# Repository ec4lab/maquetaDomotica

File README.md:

# Maqueta Domótica

El propósito de este repositorio es documentar el paso a paso de la construcción de una Maqueta domótica didáctica implementada sobre la plataforma Home Assistant.

<p align="center">

<figcaption align="center" style="margin-top: 10px; font-size: 14px; color: #555;">
    Maqueta Domótica
</figcaption>
</p>

Debido a la constante actualización de las plataformas utilizadas, en las guías se priorizarán conceptos y enfoques en lugar de un paso a paso estricto de utilización de cada herramienta, para evitar lo más posible la obsolescencia de la información.

## Estructura de carpetas

El repositorio se estructura en dos carpetas principales `docs` e `info`.

### docs

La primer carpeta contiene la documentación técnica y guías para la construcción e implementación de los dispositivos que componen la maqueta, par que puedan ser replicados y/o modificados en otras aplicaciones.

### info

Esta carpeta contiene información y algunos conceptos generales que complementan la documentación. No son aplicables directamente a la maqueta pero sirven como orientación para una mejor compresión de las aplicaciones y también brindan contexto a los dispositivos.

### Estructura actual del repositorio

```text
/maquetaDomótica
├── docs/
│   ├── maqueta/
│   ├── router-servidor/
│   ├── sv-template-multisensor/
│   ├── 
│   └── 
├── info/
│   ├── neopixels/
│   └── 
└── dev/
    └── Carpetas de alumnos durante el desarrollo
```

## Línea de Tiempo

Pasos a seguir para la construcción de la maqueta según la fecha de implementación

### 2026/08 - [docs/maqueta](docs/maqueta/)

* Construcción de la maqueta física
* Definición de las plantas y áreas  

### 2026/08 [docs/router-servidor](docs/router-servidor/)

* Construcción del soporte físico
* Configuración de la LAN en el Router
* Instalación de Home Assistant OS en una raspberryPI 4.
* Configuraciones básicas (IP estática, unidades, usuarios, mapa, App Companion)
* Asignación de áreas, plantas y habitaciones
* Primeras Aplicaciones (File Editor, ESPHome Device Builder, Tailscale)
* Mapa de la red y consideraciones para futuros dispositivos e integraciones.

### 2026/08 [docs/specs](docs/specs)

* Política de nombres de los dispositivos

### 2026/09 [docs/sv-template-multisensor](docs/sv-template-multisensor/)

* Primer dispositivo integrado a la maqueta.
* Entidades:
  * DHT11: Humedad y temperatura
  * Pulsador
  * Leds
  * Sensor de señal analógica
  * Botón de reset
* Sirve como plantilla para próximos dispositivos.

### 2026/09 [info/neopixels](info/neopixels)

* Introducción a las tiras de leds direccionables.
* Opciones de integración con ESPHome y Home Assistant

### 2026/10 [docs/control de luces](link)

### 2026/10 [docs/neopixels sala de estar](link)

## Trabajos Futuros

Protocolos  
Automatizaciones  
Pruebas  
Incidentes  
usuarios  
backups  
actualización  
seguridad  
dashboards  
dashboards adicionales
ZigBee  
Bluetooth/BLE  
ESP-NOW  
LoRa  
Protocolos industriales (ModBus / OPCua)  
KNX  
BACNet  
MQTT  
Matter  

### info dispositivos

* ESPHome
  * En Home Assistant OS
  * En ESPHome web
  * En VSCode
  * En Cursor con IA.
  * Crear un dispositivo genérico
    * Componentes básicos del dispositivo.
    * Entidades básicas del dispositivo.

## Licencia

Este proyecto está licenciado bajo la Licencia MIT.
Está permitido el uso, copia, modificaciones y distribución del software libremente, siempre que se incluya el aviso de derechos de autor original.  

Para más información, consultar el archivo [LICENSE](LICENSE)

## Contacto

**EC4lab**  
GitHub: [ec4lab](https://github.com/ec4lab)  
email: [ec4lab@gmail.com](ec4lab@gmail.com)

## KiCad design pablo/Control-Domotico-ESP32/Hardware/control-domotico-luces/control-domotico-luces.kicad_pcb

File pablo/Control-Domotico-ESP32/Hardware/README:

## 🛠️ 4. Diseño electrónico en KiCad

Para construir el módulo de domótica se diseñó una placa de circuito impreso utilizando **KiCad**, una herramienta de diseño electrónico que permite desarrollar tanto el esquemático como el PCB.

### 4.1. Diseño del esquemático

En primer lugar, se realizó el esquemático del circuito para representar las conexiones eléctricas entre el ESP32, las teclas, las resistencias, los transistores y las luces.

El diseño contempla:

- Las conexiones de las seis entradas digitales para las teclas.
- Las resistencias pull-down de 10 kΩ para establecer el nivel lógico de las entradas.
- Las seis salidas digitales destinadas al control de los transistores 2N2222A.
- Las resistencias de base de los transistores.
- La distribución de alimentación de 5 V y las conexiones de GND.
- Las borneras para facilitar la conexión externa de los distintos elementos del circuito.

El esquemático permite verificar las conexiones antes de trasladarlas a la placa física.

### 4.2. Diseño de la placa PCB

Una vez finalizado el esquemático, se desarrolló el diseño de la placa de circuito impreso (PCB) en KiCad.

En esta etapa se definieron la ubicación de los componentes, las pistas de cobre y las borneras necesarias para conectar el ESP32 con los circuitos externos.

El uso de borneras permite conectar y desconectar las teclas, las luces y la alimentación sin tener que soldar directamente cada cable a la placa. Esto facilita el montaje, las pruebas y el mantenimiento del sistema.

También se debe respetar la separación entre las pistas y dimensionar su ancho de acuerdo con las corrientes que circulan por ellas, especialmente en las líneas de alimentación de las luces.

### 4.3. Fabricación mediante grabado químico

Para fabricar la PCB se utilizará la técnica de **grabado químico con ácido**. Este procedimiento permite obtener las pistas conductoras sobre una placa revestida de cobre, eliminando el cobre de las zonas que no forman parte del circuito.

El proceso de fabricación comprende las siguientes etapas:

1. **Preparación del diseño:** revisar el PCB en KiCad y generar el patrón de las pistas para transferirlo a la placa.
2. **Preparación de la placa:** limpiar la superficie de cobre para facilitar la transferencia del diseño.
3. **Transferencia del patrón:** aplicar el diseño de las pistas sobre la placa utilizando un método de transferencia adecuado.
4. **Grabado químico:** eliminar el cobre expuesto mediante un producto de grabado apropiado, siguiendo las instrucciones de seguridad del fabricante.
5. **Limpieza y revisión:** retirar los residuos del proceso y comprobar que las pistas hayan quedado correctamente definidas, sin cortes ni cortocircuitos.
6. **Perforado y montaje:** realizar los orificios necesarios, soldar los componentes y colocar las borneras.
7. **Verificación eléctrica:** comprobar la continuidad de las pistas y la ausencia de cortocircuitos antes de conectar la alimentación y el ESP32.

Durante el grabado se deben utilizar los elementos de protección adecuados y trabajar en un lugar apropiado. El producto químico utilizado y sus residuos deben manipularse y desecharse según sus indicaciones de seguridad y la normativa local.

---

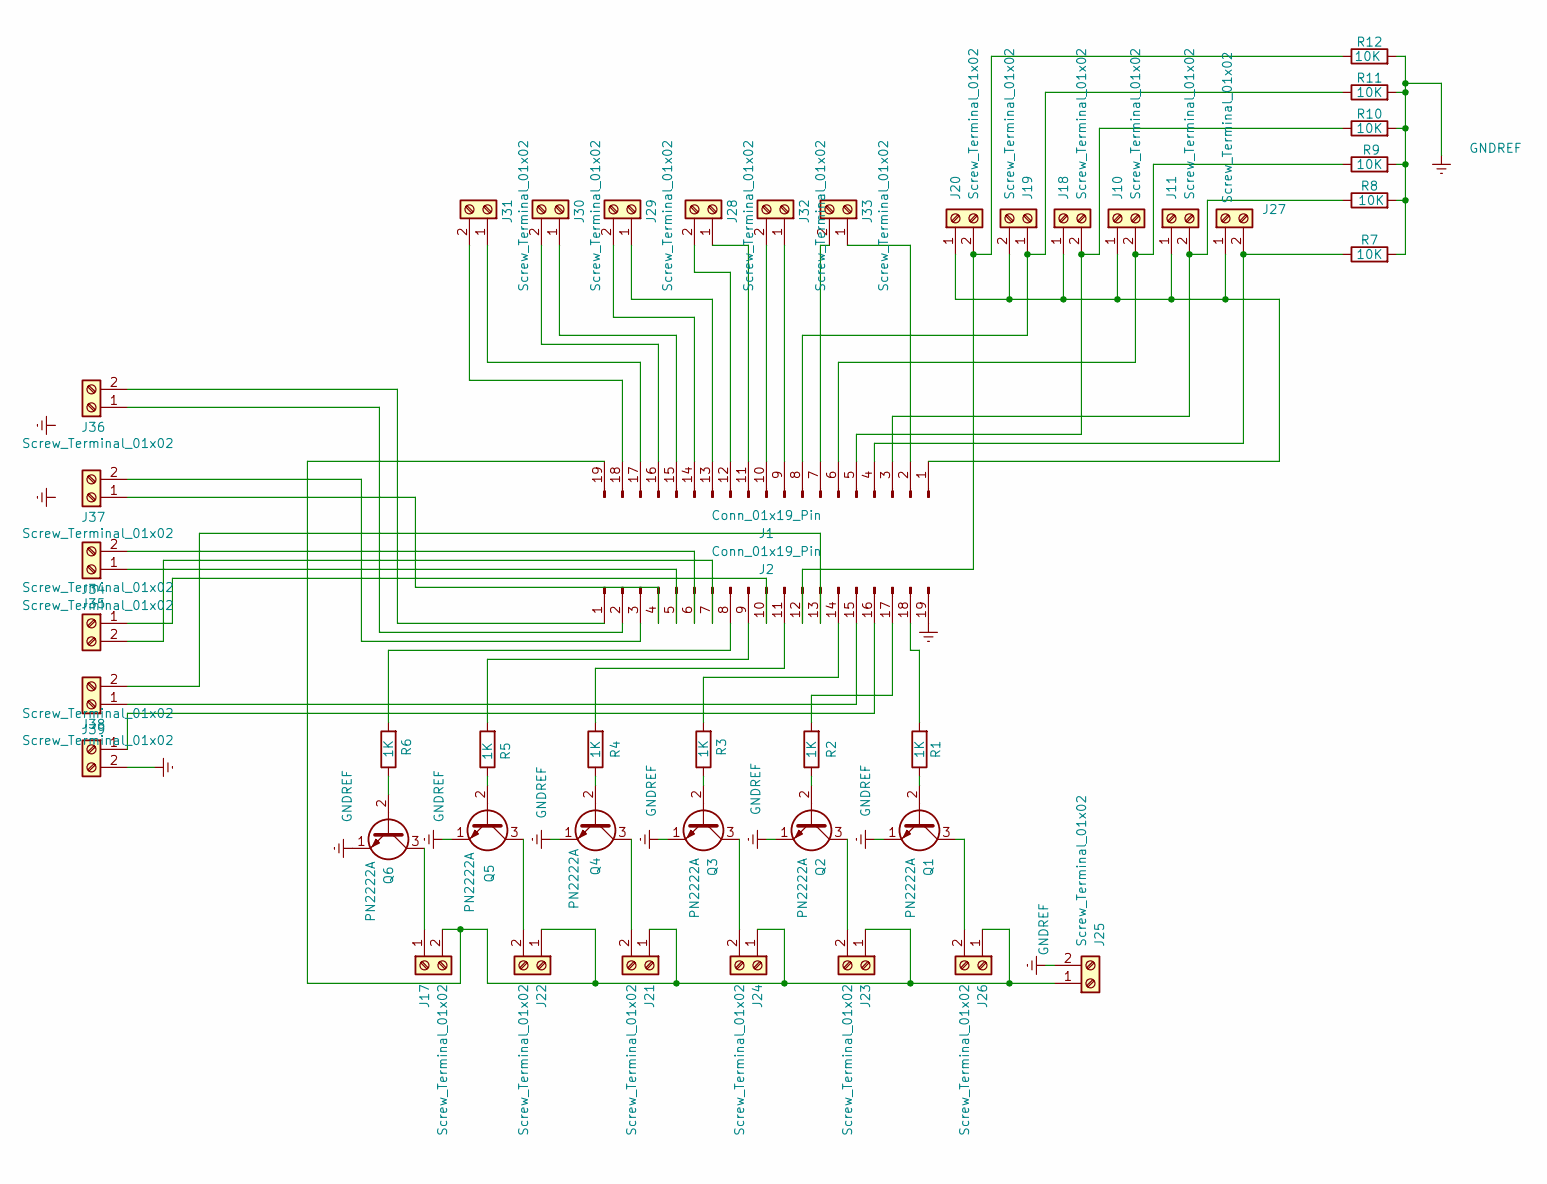
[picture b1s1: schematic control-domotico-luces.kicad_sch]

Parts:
J1, J2: Conn_01x19_Pin; PinHeader_1x19_P2.54mm_Vertical
J10, J11, J17, J18, J19, J20, J21, J22, J23, J24, J25, J26, J27, J28, J29, J30, J31, J32, J33, J34, J35, J36, J37, J38, J39: Screw_Terminal_01x02; TerminalBlock_MaiXu_MX126-5.0-02P_1x02_P5.00mm
Q1, Q2, Q3, Q4, Q5, Q6: PN2222A; TO-92_Wide
R1, R2, R3, R4, R5, R6: 1K; R_Axial_DIN0207_L6.3mm_D2.5mm_P10.16mm_Horizontal
R7, R8, R9, R10, R11, R12: 10K; R_Axial_DIN0207_L6.3mm_D2.5mm_P10.16mm_Horizontal

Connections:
GNDREF: J2.19, J25.2, J39.2, Q1.1 (E), Q2.1 (E), Q3.1 (E), Q4.1 (E), Q5.1 (E), Q6.1 (E), R7.2, R8.2, R9.2, R10.2, R11.2, R12.2
unnamed: J1.1, J10.1, J11.1, J18.1, J19.2, J20.1, J27.1
unnamed: J1.2, J33.1
unnamed: J1.3, J11.2, R8.1
unnamed: J1.4, J27.2, R7.1
unnamed: J1.5, J18.2, R10.1
unnamed: J1.6, J10.2, R9.1
unnamed: J1.7, J33.2
unnamed: J1.8, J19.1, R11.1
unnamed: J1.9, J32.1
unnamed: J1.10, J32.2
unnamed: J1.11, J28.1
unnamed: J1.12, J28.2
unnamed: J1.13, J29.1
unnamed: J1.14, J29.2
unnamed: J1.15, J30.1
unnamed: J1.16, J30.2
unnamed: J1.17, J31.1
unnamed: J1.18, J31.2
unnamed: J1.19, J17.2, J21.1, J22.1, J23.1, J24.1, J25.1, J26.1
unnamed: J2.1, J36.2
unnamed: J2.2, J36.1
unnamed: J2.3, J37.2
unnamed: J2.4, J37.1
unnamed: J2.5, J34.1
unnamed: J2.6, J34.2
unnamed: J2.7, J35.2
unnamed: J2.8, R6.2
unnamed: J2.9, R5.2
unnamed: J2.10, J35.1
unnamed: J2.11, R4.2
unnamed: J2.12, J20.2, R12.1
unnamed: J2.13, J38.2
unnamed: J2.14, R3.2
unnamed: J2.15, J38.1
unnamed: J2.16, J39.1
unnamed: J2.17, R2.2
unnamed: J2.18, R1.2
unnamed: J17.1, Q6.3 (C)
unnamed: J21.2, Q4.3 (C)
unnamed: J22.2, Q5.3 (C)
unnamed: J23.2, Q2.3 (C)
unnamed: J24.2, Q3.3 (C)
unnamed: J26.2, Q1.3 (C)
unnamed: Q1.2 (B), R1.1
unnamed: Q2.2 (B), R2.1
unnamed: Q3.2 (B), R3.1
unnamed: Q4.2 (B), R4.1
unnamed: Q5.2 (B), R5.1
unnamed: Q6.2 (B), R6.1

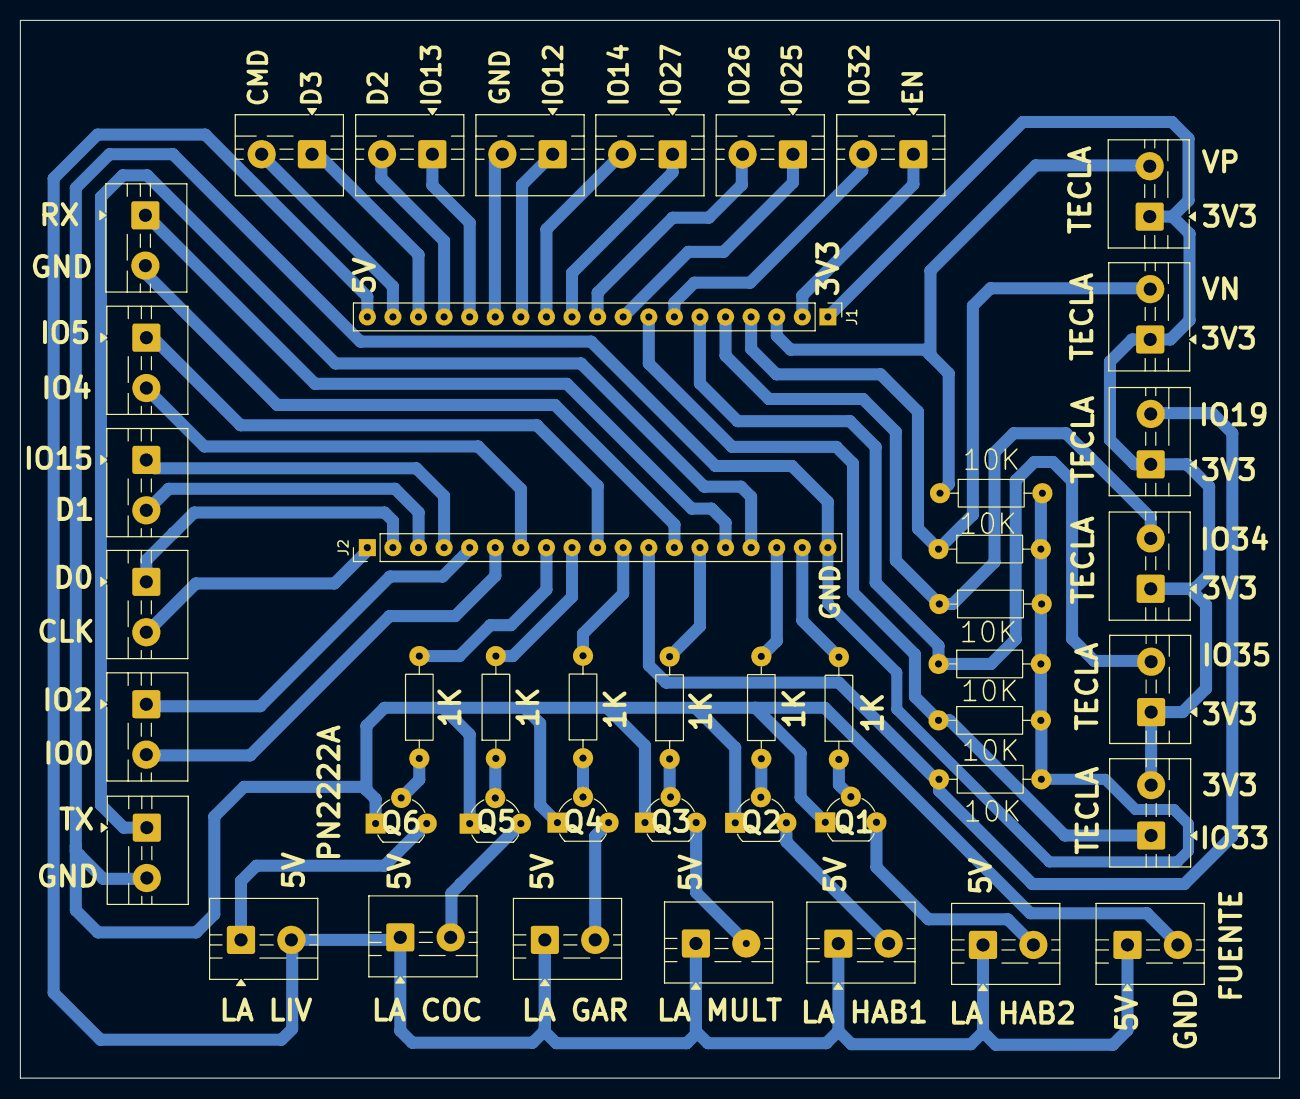
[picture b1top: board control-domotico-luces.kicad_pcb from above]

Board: 2 copper layers, 125.0 x 105.0 mm, 45 parts (0 on the bottom side), 50 nets.
